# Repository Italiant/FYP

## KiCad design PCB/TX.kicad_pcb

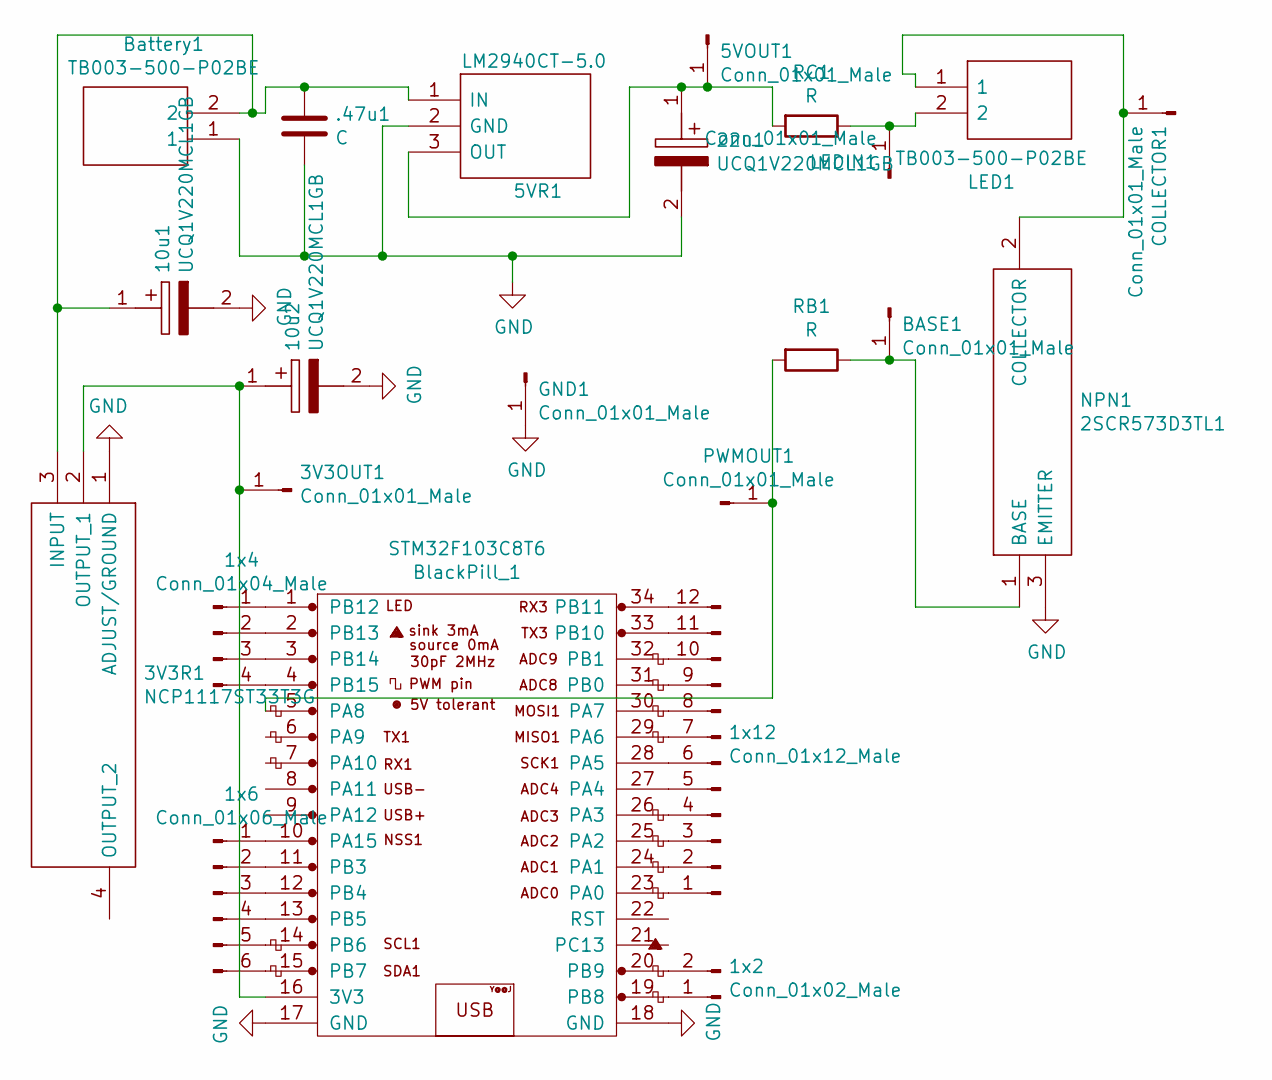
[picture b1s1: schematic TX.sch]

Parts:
1x2: Conn_01x02_Male; PinHeader_1x02_P2.54mm_Vertical
1x4: Conn_01x04_Male; PinHeader_1x04_P2.54mm_Vertical
1x6: Conn_01x06_Male; PinHeader_1x06_P2.54mm_Vertical
1x12: Conn_01x12_Male; PinHeader_1x12_P2.54mm_Vertical
3V3OUT1, 5VOUT1: Conn_01x01_Male; PinHeader_1x01_P2.54mm_Vertical
3V3R1: NCP1117ST33T3G; SOT230P700X180-4N; Mouser Part Number 863-NCP1117ST33T3G
5VR1: LM2940CT-5.0; TO254P470X1016X2222-3P; Manufacturer_Part_Number LM2940CT-5.0; Mouser Part Number 926-LM2940CT-50
10u1, 10u2, 22u1: UCQ1V220MCL1GB; CAPAE660X530N; Mouser Part Number 647-UCQ1V220MCL1GB
.47u1: C; C_1206_3216Metric_Pad1.33x1.80mm_HandSolder
BASE1: Conn_01x01_Male; PinHeader_1x01_P2.54mm_Vertical
Battery1: TB003-500-P02BE; SHDR2W100P0X500_1X2_1000X780X1030P; Mouser Part Number 490-TB003-500-P02BE
COLLECTOR1: Conn_01x01_Male; PinHeader_1x01_P2.54mm_Vertical
GND1: Conn_01x01_Male; PinHeader_1x01_P2.54mm_Vertical
LED1: TB003-500-P02BE; SHDR2W100P0X500_1X2_1000X780X1030P; Mouser Part Number 490-TB003-500-P02BE
LEDIN1: Conn_01x01_Male; PinHeader_1x01_P2.54mm_Vertical
NPN1: 2SCR573D3TL1; Mouser Part Number 755-2SCR573D3TL1
PWMOUT1: Conn_01x01_Male; PinHeader_1x01_P2.54mm_Vertical
RB1: R; R_1206_3216Metric_Pad1.30x1.75mm_HandSolder
RC1: R; R_1206_3216Metric_Pad1.30x1.75mm_HandSolder
STM32F103C8T6: BlackPill_1; YAAJ_BlackPill

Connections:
GND: 3V3R1.1 (ADJUST/GROUND), 5VR1.2 (GND), 10u1.2, 10u2.2, 22u1.2, .47u1.2, Battery1.1, GND1.1, NPN1.3 (EMITTER), STM32F103C8T6.17 (GND), STM32F103C8T6.18 (GND)
unnamed: 1x2.1, STM32F103C8T6.19 (PB8)
unnamed: 1x2.2, STM32F103C8T6.20 (PB9)
unnamed: 1x4.1, STM32F103C8T6.1 (PB12)
unnamed: 1x4.2, STM32F103C8T6.2 (PB13)
unnamed: 1x4.3, STM32F103C8T6.3 (PB14)
unnamed: 1x4.4, STM32F103C8T6.4 (PB15)
unnamed: 1x6.1, STM32F103C8T6.10 (PA15)
unnamed: 1x6.2, STM32F103C8T6.11 (PB3)
unnamed: 1x6.3, STM32F103C8T6.12 (PB4)
unnamed: 1x6.4, STM32F103C8T6.13 (PB5)
unnamed: 1x6.5, STM32F103C8T6.14 (PB6)
unnamed: 1x6.6, STM32F103C8T6.15 (PB7)
unnamed: 1x12.1, STM32F103C8T6.23 (PA0)
unnamed: 1x12.2, STM32F103C8T6.24 (PA1)
unnamed: 1x12.3, STM32F103C8T6.25 (PA2)
unnamed: 1x12.4, STM32F103C8T6.26 (PA3)
unnamed: 1x12.5, STM32F103C8T6.27 (PA4)
unnamed: 1x12.6, STM32F103C8T6.28 (PA5)
unnamed: 1x12.7, STM32F103C8T6.29 (PA6)
unnamed: 1x12.8, STM32F103C8T6.30 (PA7)
unnamed: 1x12.9, STM32F103C8T6.31 (PB0)
unnamed: 1x12.10, STM32F103C8T6.32 (PB1)
unnamed: 1x12.11, STM32F103C8T6.33 (PB10)
unnamed: 1x12.12, STM32F103C8T6.34 (PB11)
unnamed: 3V3OUT1.1, 3V3R1.2 (OUTPUT_1), 10u2.1, STM32F103C8T6.16 (3V3)
unnamed: 5VOUT1.1, 5VR1.3 (OUT), 22u1.1, RC1.2
unnamed: 3V3R1.3 (INPUT), 5VR1.1 (IN), 10u1.1, .47u1.1, Battery1.2
unnamed: BASE1.1, NPN1.1 (BASE), RB1.1
unnamed: COLLECTOR1.1, LED1.1, NPN1.2 (COLLECTOR)
unnamed: LED1.2, LEDIN1.1, RC1.1
unnamed: PWMOUT1.1, RB1.2, STM32F103C8T6.5 (PA8)

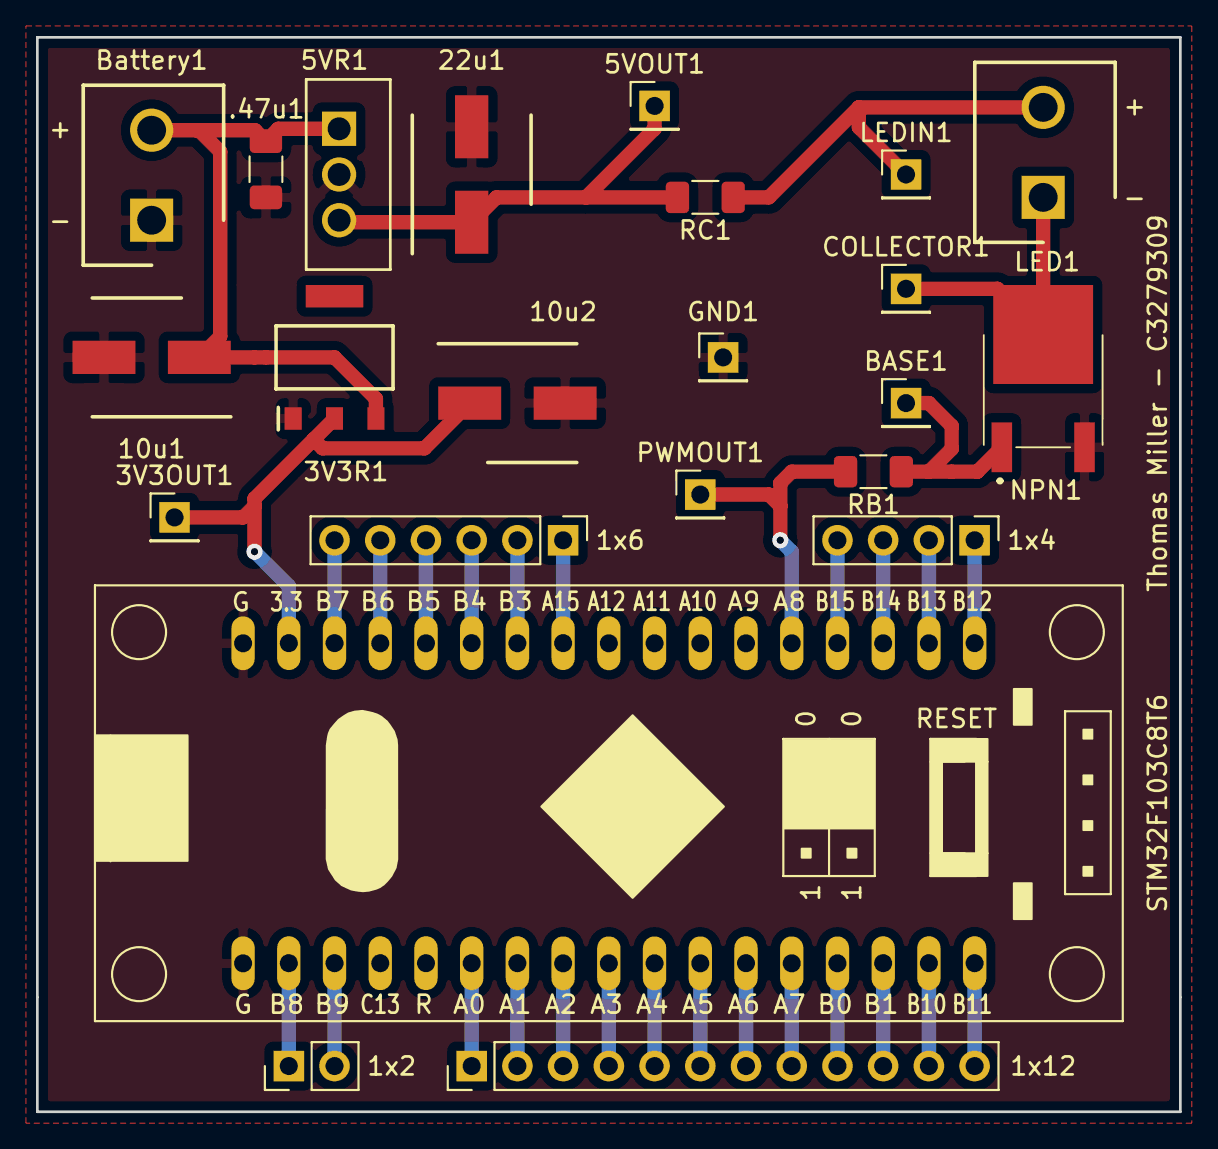
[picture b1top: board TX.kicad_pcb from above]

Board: 2 copper layers, 63.5 x 59.7 mm, 23 parts (0 on the bottom side), 32 nets.

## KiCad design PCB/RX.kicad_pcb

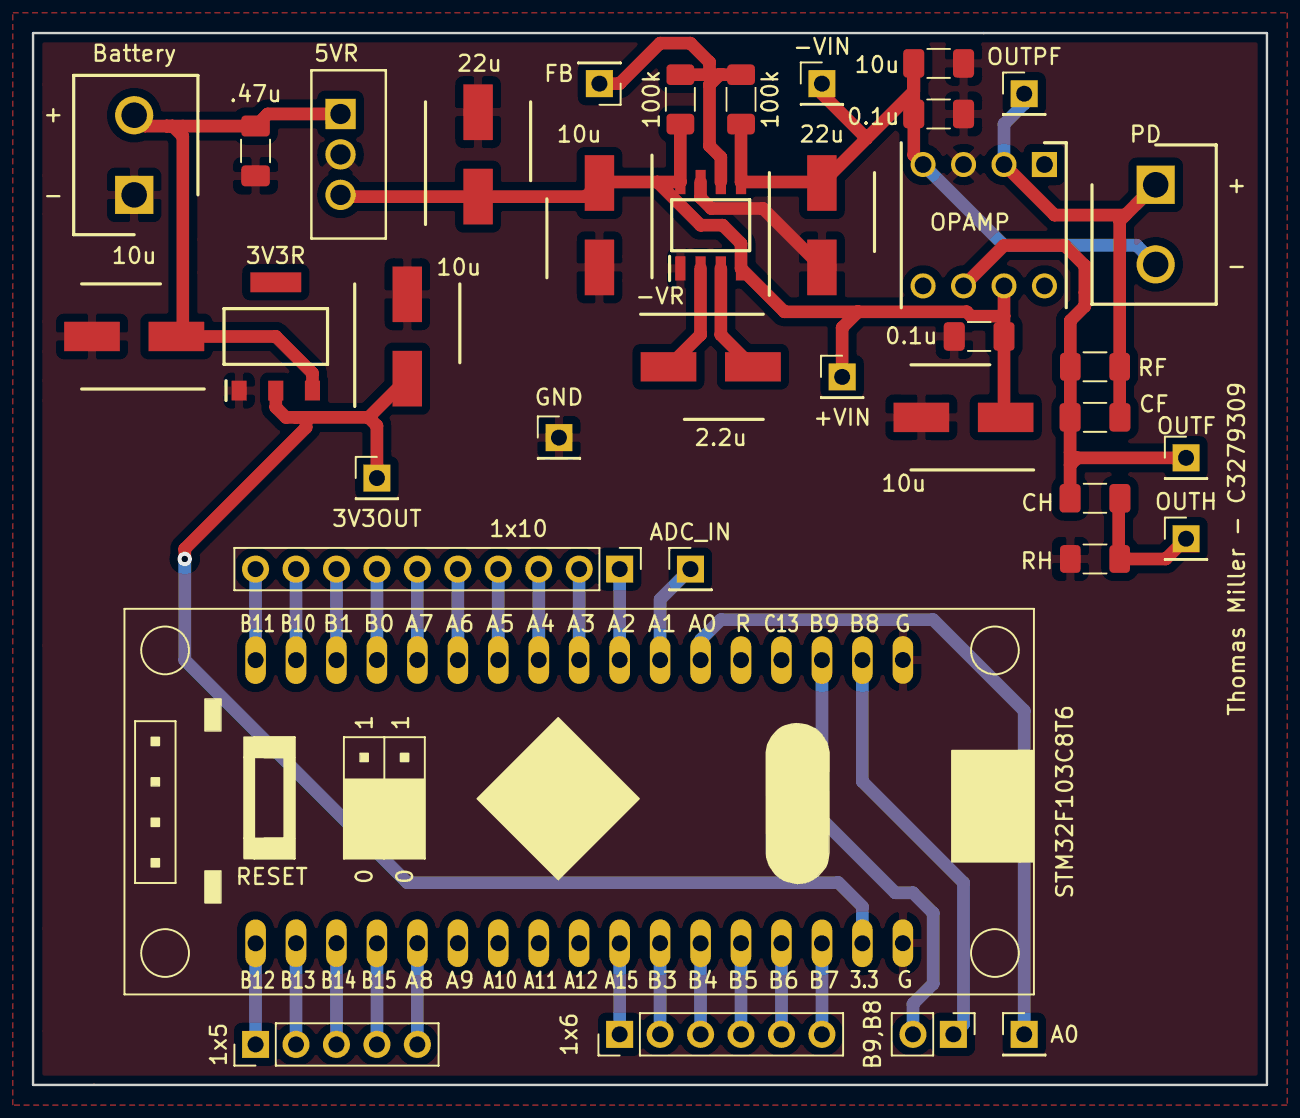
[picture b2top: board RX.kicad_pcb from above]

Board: 2 copper layers, 77.5 x 66.0 mm, 38 parts (0 on the bottom side), 36 nets.

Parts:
0.1u, 0.1u#2, 10u#5, .47u: C; C_1206_3216Metric_Pad1.33x1.80mm_HandSolder
1x5: Conn_01x05_Male; PinHeader_1x05_P2.54mm_Vertical
1x6: Conn_01x06_Male; PinHeader_1x06_P2.54mm_Vertical
1x10: Conn_01x10_Male; PinHeader_1x10_P2.54mm_Vertical
2.2u, 10u, 10u#2, 10u#3, 10u#4, 22u, 22u#2: UCQ1V220MCL1GB; CAPAE660X530N
3V3OUT: Conn_01x01_Male; PinHeader_1x01_P2.54mm_Vertical
3V3R: NCP1117ST33T3G; SOT230P700X180-4N
5VR: LM2940CT-5.0; TO254P470X1016X2222-3P
100k, 100k#2: R; R_1206_3216Metric_Pad1.30x1.75mm_HandSolder
+VIN: Conn_01x01_Male; PinHeader_1x01_P2.54mm_Vertical
-VIN: Conn_01x01_Male; PinHeader_1x01_P2.54mm_Vertical
-VR: MAX1673ESA+; SOIC127P600X175-8N
A0: Conn_01x01_Male; PinHeader_1x01_P2.54mm_Vertical
ADC_IN: Conn_01x01_Male; PinHeader_1x01_P2.54mm_Vertical
B9,B8: Conn_01x02_Male; PinHeader_1x02_P2.54mm_Vertical
Battery: TB003-500-P02BE; SHDR2W100P0X500_1X2_1000X780X1030P
CF: C; C_1206_3216Metric_Pad1.33x1.80mm_HandSolder
CH: C; C_1206_3216Metric_Pad1.33x1.80mm_HandSolder
FB: Conn_01x01_Male; PinHeader_1x01_P2.54mm_Vertical
GND: Conn_01x01_Male; PinHeader_1x01_P2.54mm_Vertical
OPAMP: AD8055ANZ; DIPS762W61P254L1016H525Q8N
OUTF: Conn_01x01_Male; PinHeader_1x01_P2.54mm_Vertical
OUTH: Conn_01x01_Male; PinHeader_1x01_P2.54mm_Vertical
OUTPF: Conn_01x01_Male; PinHeader_1x01_P2.54mm_Vertical
PD: TB003-500-P02BE; SHDR2W100P0X500_1X2_1000X780X1030P
RF: R; R_1206_3216Metric_Pad1.30x1.75mm_HandSolder
RH: R; R_1206_3216Metric_Pad1.30x1.75mm_HandSolder
STM32F103C8T6: BlackPill_1; YAAJ_BlackPill

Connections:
GND: 0.1u.2, 0.1u#2.1, 3V3R.1, 5VR.2, 10u.2, 10u#2.2, 10u#3.2, 10u#4.2, 10u#5.1, 22u.2, 22u#2.1, -VR.1, -VR.7, .47u.1, Battery.1, GND.1, OPAMP.3, RH.2, STM32F103C8T6.17, STM32F103C8T6.18
unnamed: 1x5.1, STM32F103C8T6.1
unnamed: 1x5.2, STM32F103C8T6.2
unnamed: 1x5.3, STM32F103C8T6.3
unnamed: 1x5.4, STM32F103C8T6.4
unnamed: 1x5.5, STM32F103C8T6.5
unnamed: 1x6.1, STM32F103C8T6.10
unnamed: 1x6.2, STM32F103C8T6.11
unnamed: 1x6.3, STM32F103C8T6.12
unnamed: 1x6.4, STM32F103C8T6.13
unnamed: 1x6.5, STM32F103C8T6.14
unnamed: 1x6.6, STM32F103C8T6.15
unnamed: 1x10.1, STM32F103C8T6.25
unnamed: 1x10.2, STM32F103C8T6.26
unnamed: 1x10.3, STM32F103C8T6.27
unnamed: 1x10.4, STM32F103C8T6.28
unnamed: 1x10.5, STM32F103C8T6.29
unnamed: 1x10.6, STM32F103C8T6.30
unnamed: 1x10.7, STM32F103C8T6.31
unnamed: 1x10.8, STM32F103C8T6.32
unnamed: 1x10.9, STM32F103C8T6.33
unnamed: 1x10.10, STM32F103C8T6.34
unnamed: 2.2u.1, -VR.2
unnamed: 2.2u.2, -VR.3
unnamed: 3V3OUT.1, 3V3R.2, 10u#2.1, STM32F103C8T6.16
unnamed: 100k.2, 100k#2.1, -VR.6, FB.1
unnamed: 0.1u.1, 5VR.3, 10u#3.1, 10u#4.1, 22u.1, 100k.1, +VIN.1, -VR.4, -VR.8, OPAMP.7
unnamed: 0.1u#2.2, 10u#5.2, 22u#2.2, 100k#2.2, -VIN.1, -VR.5, OPAMP.4, PD.2
unnamed: 3V3R.3, 5VR.1, 10u.1, .47u.2, Battery.2
unnamed: A0.1, STM32F103C8T6.23
unnamed: ADC_IN.1, STM32F103C8T6.24
unnamed: B9,B8.1, STM32F103C8T6.19
unnamed: B9,B8.2, STM32F103C8T6.20
unnamed: CF.1, OPAMP.2, OUTPF.1, PD.1, RF.1
unnamed: CF.2, CH.2, OPAMP.6, OUTF.1, RF.2
unnamed: CH.1, OUTH.1, RH.1

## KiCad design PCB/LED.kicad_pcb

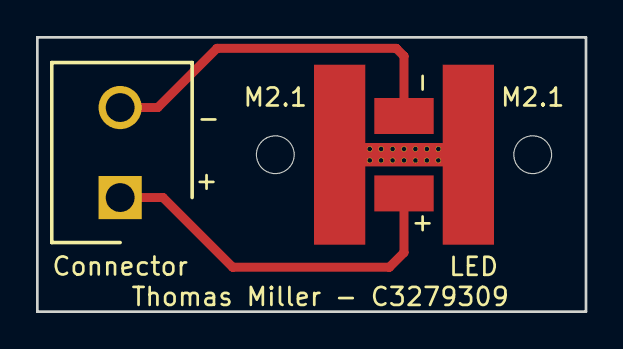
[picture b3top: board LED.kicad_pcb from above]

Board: 2 copper layers, 30.5 x 15.2 mm, 4 parts (0 on the bottom side), 2 nets.

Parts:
Connector: TB003-500-P02BE-SamacSys_Parts; SHDR2W100P0X500_1X2_1000X780X1030P
LED: XPEBGR-L1-0000-00G03-SamacSys_Parts; LED_Thermal
M2.1, M2.1#2: MountingHole_2.1mm

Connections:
unnamed: Connector.1, LED.2
unnamed: Connector.2, LED.1
